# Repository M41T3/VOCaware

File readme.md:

# What is VOCaware?

VOCaware is a small device that measures volatile organic components (VOCs) in the ambient air and indicates potential unhealthy exposure.

VOCs are released during 3D printing caused by the melting process of plastic filaments. The exposure depends on the material and the melting temperature. Since there are no long term studies on the implications of VOC exposure to the human being it‘s reasonable to mitigate the risk of  potential health issues by avoiding these gases.

# Features

- WIFI enabled microcontroller (ESP32-S3) to transmit sensor data wirelessly or via serial communication
- Sensirion SGP40 VOC sensor 
- Sensirion SHT40 temperature and humdity sensor to calibrate VOC sensor
- WS2812B LED to indicate intensity of exposure
- USB C plug to power and program device
- Compact PCB design (40 mm x 30 mm)
- Compact housing ( 43 mm x 33 mm x 11 mm) with magnets to easily attach to metal objects

# PCB

- 2 layers
- 40 x 30 mm
- JLCPCB production files available

# Housing

The lid simply clips to the bottom part of the housing. On the backside are holes for magnets.

Frontside:

Backside: 

# VOC Indication

Color code of the RGB LED is programmed according to Sensirions SGP40 VOC index scale to show a trend of the intensity over time. The devices needs severeal seconds to set up. During this, the LED blinks green.  

| LED Color| VOC Index | Exposure |
|----------|----------|----------|
| blue     | 0 - 70  | decreased |
| green    | 70 - 140 | OK |
| yellow    | 131 - 210 | slightly increased |
| orange    | 221 - 280 | increased |
| red    | 281 - 350 | significantly increased |
| red blink  | 351 - 500 | concerningly increased  |

# Compatible to Bambu Lab P1S 3D Printer

Device fits in enclosure of the P1S printer and can be power directly from the internal USB plug. Please print the housing with PETG filament or similar so that it withstands the increased temperatures in the chamber.

The VOCaware is also visible in the camera view of the Bambu Studio interface:

# What's Next
Ideas for improvements and features:

- Control Bento Box via VOCaware GPIO according to VOC Index
- Connect to MQTT Broker

# Known Issues

Unfortunatly the ground layer is not sufficiently interconnected. It can be easily fixed by soldering a short wire from the GND test pin to the ground zone as shown in the image:

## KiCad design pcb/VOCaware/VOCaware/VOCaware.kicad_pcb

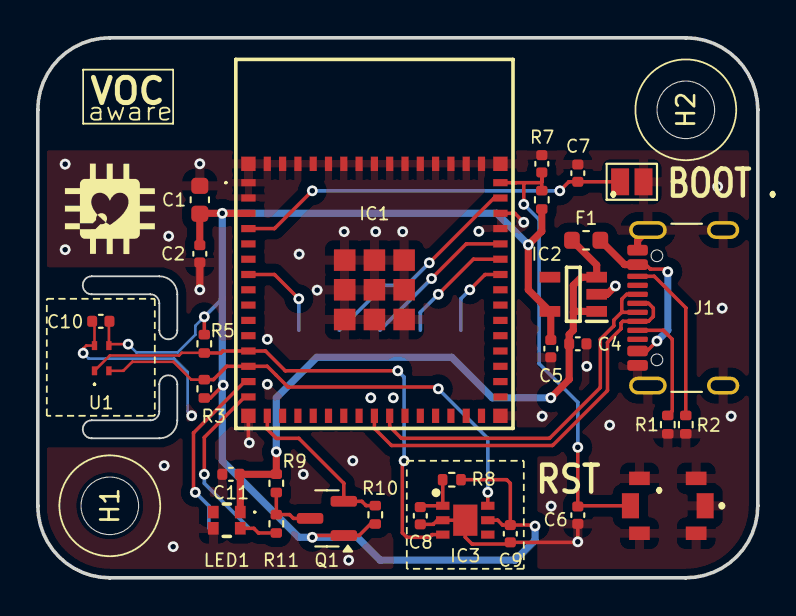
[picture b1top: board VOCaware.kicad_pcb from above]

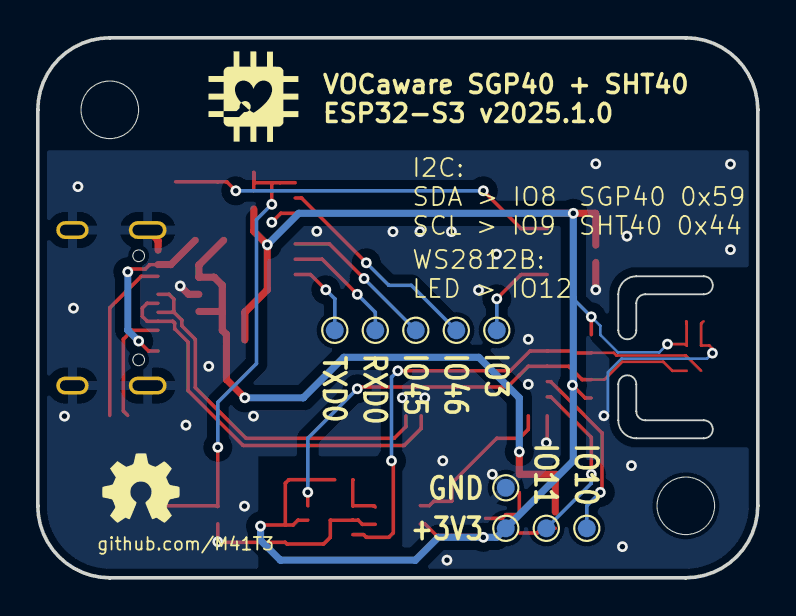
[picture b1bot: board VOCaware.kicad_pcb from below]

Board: 2 copper layers, 40.0 x 30.0 mm, 41 parts (9 on the bottom side), 23 nets.

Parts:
+3V3: Conn_01x01_Socket; TestPoint_Pad_D1.0mm
C1: 22uF; C_0603_1608Metric
C2, C3, C6, C7, C10, C11: 0.1uF; C_0402_1005Metric
C4: 10uF; C_0402_1005Metric
C5, C8, C9: 1uF; C_0402_1005Metric
F1: SMD0603-050; Fuse_0603_1608Metric
GND: Conn_01x01_Socket; TestPoint_Pad_D1.0mm
H1, H2: MountingHole; MountingHole_3.2mm_M3_DIN965
IC1: ESP32-S3-MINI-1-N8; ESP32S3MINI1N8
IC2: AP2112K-3.3TRG1; SOT95P285X140-5N
IC3: SGP40-D-R4; SON80P244X244X95-7N
IO3, IO10, IO11, IO45, IO46: Conn_01x01_Socket; TestPoint_Pad_D1.0mm
J1: USB_C_Receptacle_USB2.0_16P; USB_C_Receptacle_GCT_USB4105-xx-A_16P_TopMnt_Horizontal
LED1: XL-0807RGBC-WS2812B; XL0807RGBCWS2812B
Q1: BSS138BK; SOT-23
R1, R2: 5.1k 1%; R_0402_1005Metric
R3, R5: 4.7k; R_0402_1005Metric
R7, R9, R10: 10k; R_0402_1005Metric
R8: 4.7; R_0402_1005Metric
R11: 470; R_0402_1005Metric
RST   .: PTS820J25MSMTRLFS
RXD0: Conn_01x01_Socket; TestPoint_Pad_D1.0mm
SW1: SW_Push; SolderJumper-2_P1.3mm_Open_Pad1.0x1.5mm
TXD0: Conn_01x01_Socket; TestPoint_Pad_D1.0mm
U1: SHT40-AD1F-R2; SHT40AD1FR2

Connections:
+3V3: +3V3.1, C1.1, C2.1, C5.1, C9.1, C10.1, IC1.3 (3V3), IC2.5 (VOUT), IC3.5 (VDDH), Q1.1 (G), R3.1, R5.1, R7.1, R8.1, R10.1, U1.3 (VDD)
+5V: C4.1, C11.1, F1.1, IC2.1 (VIN), IC2.3 (EN), LED1.1 (VDD), R9.2
EN: C3.1, C6.1, IC1.45 (EN), R7.2, RST ..2 (N.O.)
GND: C1.2, C2.2, C3.2, C4.2, C5.2, C6.2, C7.2, C8.2, C9.2, C10.2, C11.2, GND.1, IC1.1 (GND_1), IC1.2 (GND_2), IC1.42 (GND_3), IC1.43 (GND_4), IC1.46 (GND_5), IC1.47 (GND_6), IC1.48 (GND_7), IC1.49 (GND_8), IC1.50 (GND_9), IC1.51 (GND_10), IC1.52 (GND_11), IC1.53 (GND_12), IC1.54 (GND_13), IC1.55 (GND_14), IC1.56 (GND_15), IC1.57 (GND_16), IC1.58 (GND_17), IC1.59 (GND_18), IC1.60 (GND_19), IC1.61 (GND_20), IC1.62 (GND_21), IC1.63 (GND_22), IC1.64 (GND_23), IC1.65 (GND_24), IC1.66 (GND_25), IC1.67 (GND_26), IC1.68 (GND_27), IC1.69 (GND_28), IC1.70 (GND_29), IC1.71 (GND_30), IC1.72 (GND_31), IC1.73 (GND_32), IC2.2 (GND), IC3.2 (VSS), IC3.7 (EP), J1.A1 (GND), J1.A12 (GND), J1.B1 (GND), J1.B12 (GND), J1.S1 (SHIELD), LED1.3 (GND), R1.1, R2.1, RST ..1 (COM), RST ..G1 (GND_1), RST ..G2 (GND_2), RST ..G3 (GND_3), RST ..G4 (GND_4), SW1.1, U1.4 (VSS)
I045_S: IC1.41 (IO45), IO45.1
I046_S: IC1.44 (IO46), IO46.1
IO0: C7.1, IC1.4 (IO0), SW1.2
IO3_S: IC1.7 (IO3), IO3.1
IO8_SDA0: IC1.12 (IO8), IC3.3 (SDA), R5.2, U1.1 (SDA)
IO9_SCL0: IC1.13 (IO9), IC3.6 (SCL), R3.2, U1.2 (SCL)
IO10: IC1.14 (IO10), IO10.1
IO11: IC1.15 (IO11), IO11.1
IO12: IC1.16 (IO12), Q1.2 (S), R10.2
LED_SIG: Q1.3 (D), R9.1, R11.1
unnamed: F1.2, J1.A4 (VBUS), J1.A9 (VBUS), J1.B4 (VBUS), J1.B9 (VBUS)
unnamed: C8.1, IC3.1 (VDD), R8.2
unnamed: J1.A5 (CC1), R1.2
unnamed: J1.B5 (CC2), R2.2
unnamed: LED1.4 (DIN), R11.2
RXD0: IC1.40 (RXD0), RXD0.1
TXD0: IC1.39 (TXD0), TXD0.1
USB_D+: IC1.24 (IO20), J1.A6 (D+), J1.B6 (D+)
USB_D-: IC1.23 (IO19), J1.A7 (D-), J1.B7 (D-)

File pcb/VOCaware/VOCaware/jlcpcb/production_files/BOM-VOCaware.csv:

Comment,Designator,Footprint,LCSC,Quantity
BSS138BK,Q1,SOT-23,C112239,1
0.1uF,"C10,C11,C2,C3,C6,C7",C_0402_1005Metric,C1525,6
10uF,C4,C_0402_1005Metric,C15525,1
USB_C_Receptacle_USB2.0_16P,J1,USB_C_Receptacle_GCT_USB4105-xx-A_16P_TopMnt_Horizontal,C165948,1
SW_Push,SW1,SolderJumper-2_P1.3mm_Open_Pad1.0x1.5mm,C221900,1
470,R11,R_0402_1005Metric,C25117,1
4.7,R8,R_0402_1005Metric,C25121,1
10k,"R10,R7,R9",R_0402_1005Metric,C25744,3
4.7k,"R3,R5",R_0402_1005Metric,C25900,2
5.1k 1%,"R1,R2",R_0402_1005Metric,C25905,2
SGP40-D-R4,IC3,SON80P244X244X95-7N,C2874215,1
ESP32-S3-MINI-1-N8,IC1,ESP32S3MINI1N8,C2913206,1
XL-0807RGBC-WS2812B,LED1,XL0807RGBCWS2812B,C3646929,1
AP2112K-3.3TRG1,IC2,SOT95P285X140-5N,C51118,1
1uF,"C5,C8,C9",C_0402_1005Metric,C52923,3
22uF,C1,C_0603_1608Metric,C59461,1
SMD0603-050,F1,Fuse_0603_1608Metric,C69679,1
SHT40-AD1F-R2,U1,SHT40AD1FR2,C7461846,1

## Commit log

2025-11-16 typo
2025-11-16 fixed image issue
2025-11-23 correct readme.md
2025-11-25 improved led colors
